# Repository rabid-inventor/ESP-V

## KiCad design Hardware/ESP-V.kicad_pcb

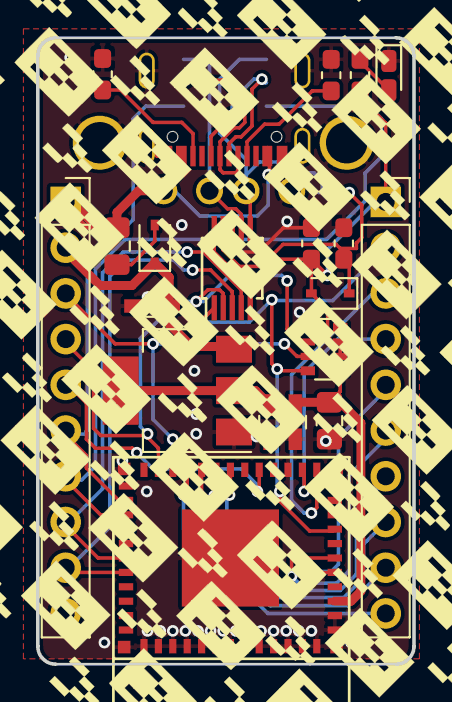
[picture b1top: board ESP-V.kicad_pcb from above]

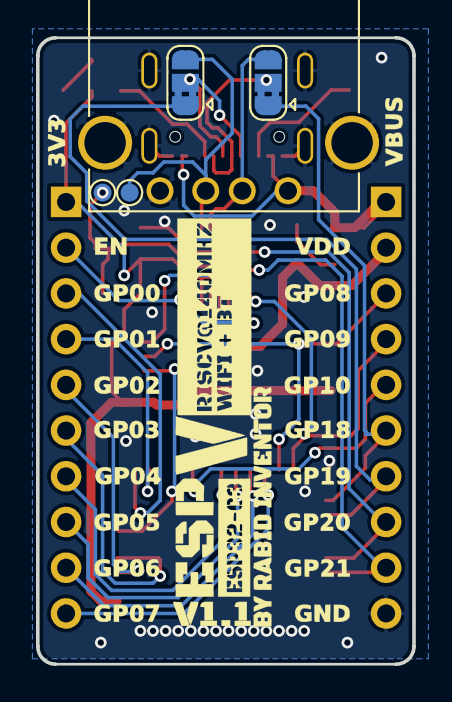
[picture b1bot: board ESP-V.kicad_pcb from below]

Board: 2 copper layers, 20.9 x 34.8 mm, 25 parts (5 on the bottom side), 29 nets.

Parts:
C4, C7: 1uF; C_0603_HandSoldering
C20: 10uF; C_0805_2012Metric_Pad1.15x1.40mm_HandSolder
C23: 100nF; C_0603_HandSoldering
C25, C26: 100nF; C_0603_1608Metric_Pad1.05x0.95mm_HandSolder
D1, D4: D_Schottky; D_SOD-323
D2: LED; LED_0603_1608Metric_Castellated
J1: USB_C_Receptacle_USB2.0; VACON_CSP_USC16_TR
J2, J3: Conn_01x10_Female; PinSocket_1x10_P2.54mm_Vertical
J4: USB_A
JP1, JP2: SolderJumper_3_Bridged12; SolderJumper-3_P1.3mm_Bridged2Bar12_RoundedPad1.0x1.5mm
L1: L_Small; L_0805_2012Metric_Pad1.15x1.40mm_HandSolder
R1, R2: 5k; R_0603_1608Metric_Pad1.05x0.95mm_HandSolder
R3: R_Small; R_0603_1608Metric_Pad1.05x0.95mm_HandSolder
RN1: 10k 5%; R_Array_Convex_4x0603
TP1: CH_BL_SEL; TestPoint_Pad_D1.0mm
TP2: PROGVCC; TestPoint_Pad_D1.0mm
U1: CH552E; MSOP-10_3x3mm_P0.5mm
U2: NCP1117-3.3_SOT223; SOT-223-3_TabPin2
U3: ESP32-C3-MINI-1; ESP32-c3-mini1

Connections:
+3V3: C7.1, C20.1, C23.1, C25.1, D4.2, J2.1, R3.1, RN1.5, RN1.6, RN1.7, U1.5, U1.10, U2.2, U3.3
/BLSEL: J3.4, RN1.2, U1.2, U3.23
/CC1: J1.A5, R2.2
/CC2: J1.B5, R1.2
/CHUSB+: J4.3, JP2.3, TP1.1, U1.6
/CHUSB-: J4.2, JP1.3, U1.7
/ESPUSB+: J3.7, JP2.1, U3.27
/ESPUSB-: J3.6, JP1.1, U3.26
/ESP_ENABLE: J2.2, RN1.4, U1.1, U3.8
/ESP_RX: J3.8, U1.4, U3.30
/ESP_TX: J3.9, U1.3, U3.31
/GP00: J2.3, U3.12
/GP01: J2.4, U3.13
/GP02: J2.5, U3.5
/GP03: J2.6, U3.6
/GP04: J2.7, U3.18
/GP05: J2.8, U3.19
/GP06: J2.9, U3.20
/GP07: J2.10, U3.21
/GP08: J3.3, RN1.3, U3.22
/GP10: J3.5, U3.16
GND: C4.2, C7.2, C20.2, C23.2, C25.2, C26.2, D2.1, J1.1, J1.A1, J1.A12, J1.B1, J1.B12, J3.10, J4.4, J4.5, R1.1, R2.1, U1.8, U2.1, U3.1, U3.2, U3.11, U3.14, U3.49
unnamed: C26.1, D4.1, TP2.1, U1.9
unnamed: D1.2, L1.1
unnamed: D2.2, R3.2
unnamed: J1.A6, J1.B6, JP2.2
unnamed: J1.A7, J1.B7, JP1.2
VBUS: J1.A4, J1.A9, J1.B4, J1.B9, J3.1, J4.1, L1.2
VDD: C4.1, D1.1, J3.2, U2.3

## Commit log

2020-12-11 inital comit
2020-12-15 finished routing + front silk
2020-12-16 ready to order needs final check
2020-12-21 redesigning to take module
2021-02-12 v1.1 ready to order
